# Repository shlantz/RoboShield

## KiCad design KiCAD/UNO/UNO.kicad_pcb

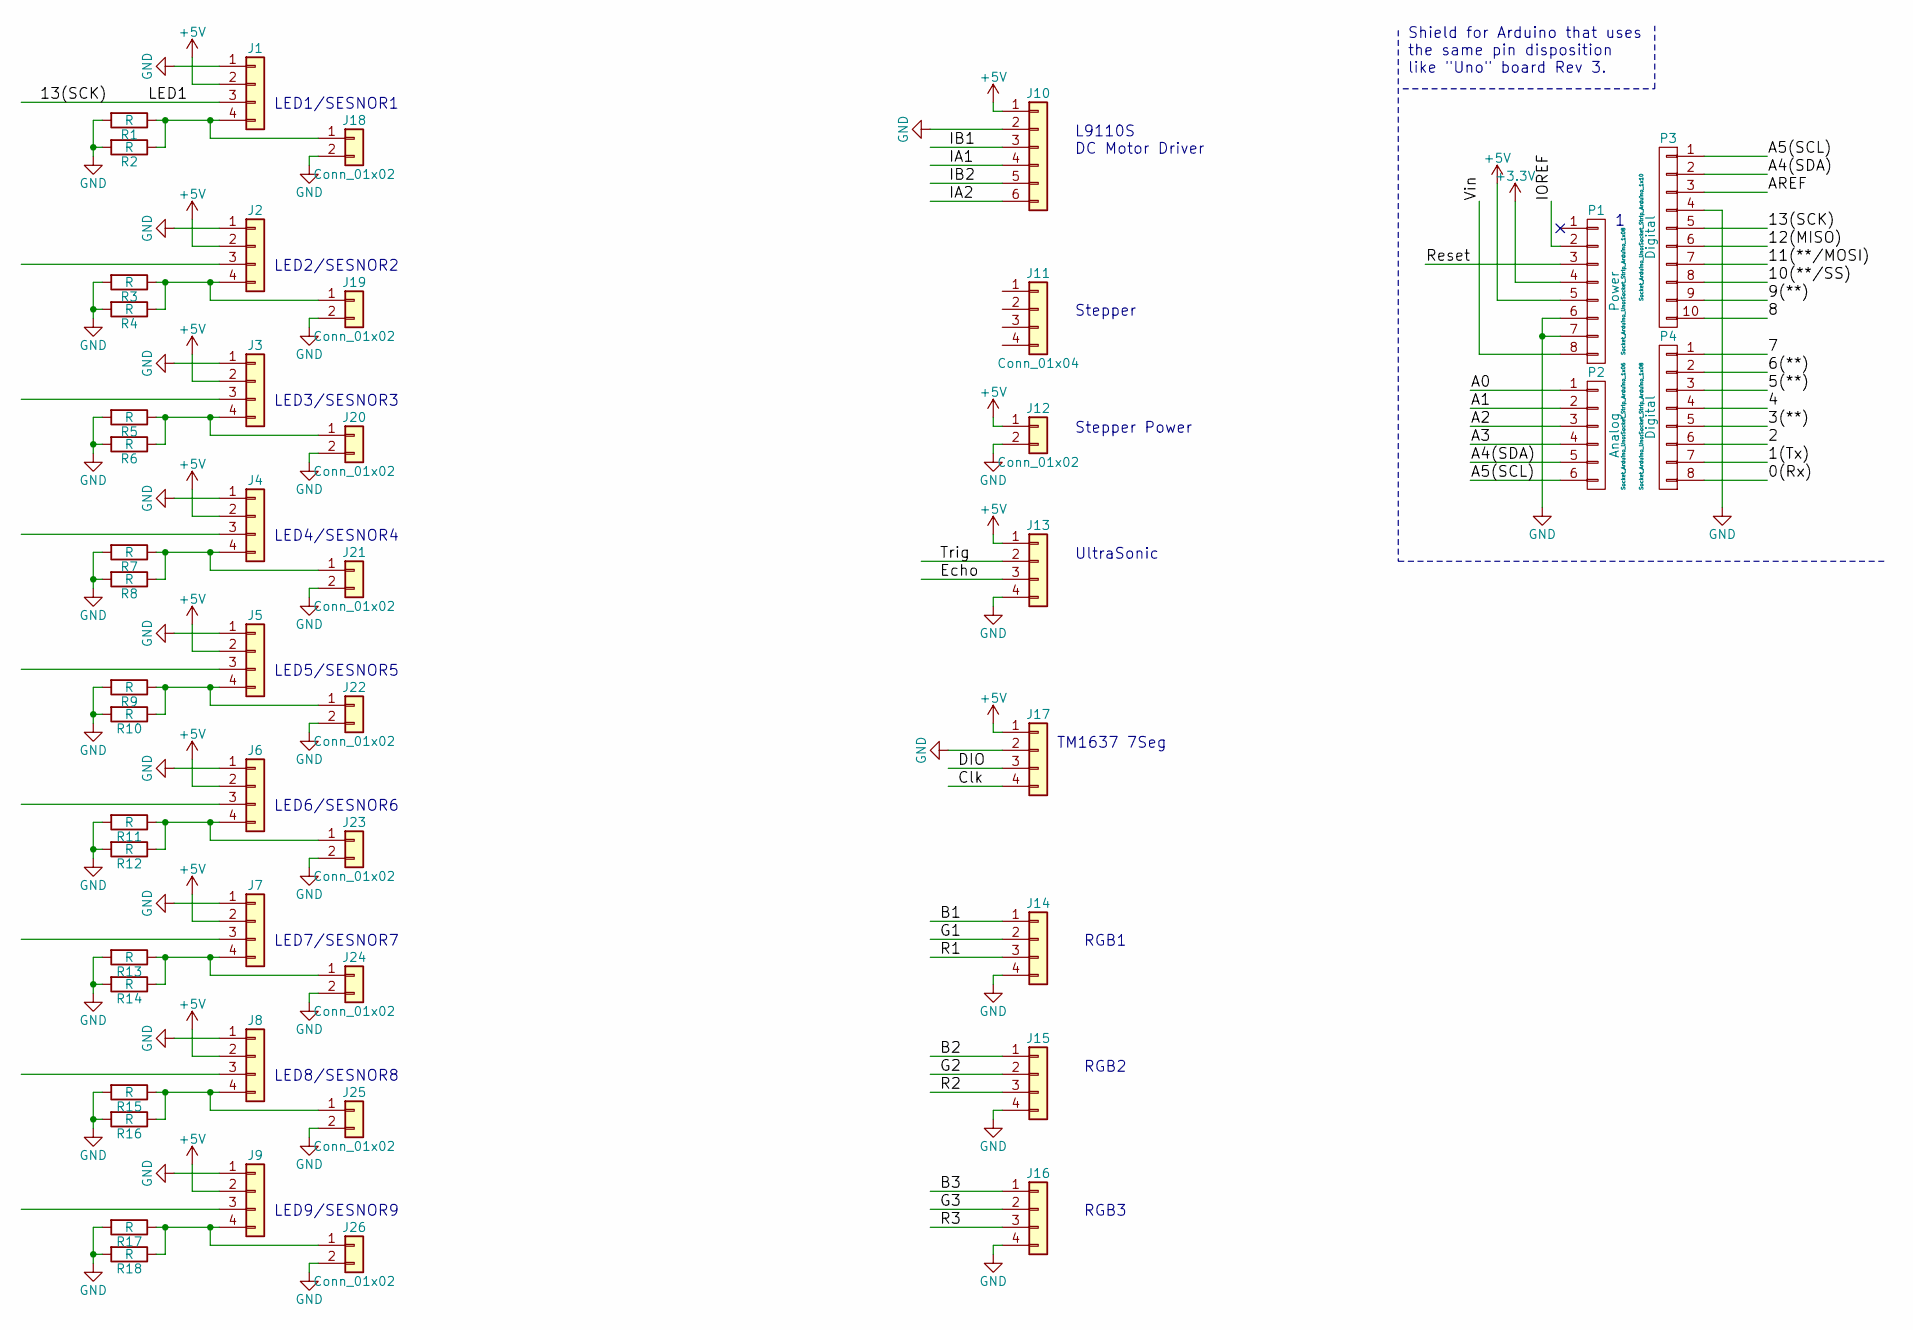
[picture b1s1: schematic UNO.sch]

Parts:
J1, J2, J3, J4, J5, J6, J7, J8, J9, J14, J15, J16, J17: Conn_01x04; Socket_Strip_Angled_1x04_Pitch2.54mm
J10: Conn_01x06; Socket_Strip_Straight_1x06_Pitch2.54mm
J11, J13: Conn_01x04; Socket_Strip_Straight_1x04_Pitch2.54mm
J12: Conn_01x02; Socket_Strip_Straight_1x02_Pitch2.54mm
J18, J19, J20, J21, J22, J23, J24, J25, J26: Conn_01x02; Pin_Header_Straight_1x02_Pitch2.54mm
P1: Power; Socket_Strip_Arduino_1x08
P2: Analog; Socket_Strip_Arduino_1x06
P3: Digital; Socket_Strip_Arduino_1x10
P4: Digital; Socket_Strip_Arduino_1x08
R1, R3, R5, R7, R9, R11, R13, R15, R17: R; R_0603_HandSoldering
R2, R4, R6, R8, R10, R12, R14, R16, R18: R; R_Axial_DIN0204_L3.6mm_D1.6mm_P5.08mm_Horizontal

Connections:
+3V3: P1.4
+5V: J1.2, J2.2, J3.2, J4.2, J5.2, J6.2, J7.2, J8.2, J9.2, J10.1, J12.1, J13.1, J17.1, P1.5
/0(Rx): P4.8
/1(Tx): P4.7
/2: P4.6
/3(**): P4.5
/4: P4.4
/5(**): P4.3
/6(**): P4.2
/7: P4.1
/8: P3.10
/9(**): P3.9
/10(**/SS): P3.8
/11(**/MOSI): P3.7
/12(MISO): P3.6
/13(SCK): J1.3, P3.5
/A0: P2.1
/A1: P2.2
/A2: P2.3
/A3: P2.4
/A4(SDA): P2.5, P3.2
/A5(SCL): P2.6, P3.1
/AREF: P3.3
/B1: J14.1
/B2: J15.1
/B3: J16.1
/Clk: J17.4
/DIO: J17.3
/Echo: J13.3
/G1: J14.2
/G2: J15.2
/G3: J16.2
/IA1: J10.4
/IA2: J10.6
/IB1: J10.3
/IB2: J10.5
/IOREF: P1.2
/R1: J14.3
/R2: J15.3
/R3: J16.3
/Reset: P1.3
/Trig: J13.2
/Vin: P1.8
GND: J1.1, J2.1, J3.1, J4.1, J5.1, J6.1, J7.1, J8.1, J9.1, J10.2, J12.2, J13.4, J14.4, J15.4, J16.4, J17.2, J18.2, J19.2, J20.2, J21.2, J22.2, J23.2, J24.2, J25.2, J26.2, P1.6, P1.7, P3.4, R1.2, R2.2, R3.2, R4.2, R5.2, R6.2, R7.2, R8.2, R9.2, R10.2, R11.2, R12.2, R13.2, R14.2, R15.2, R16.2, R17.2, R18.2
unnamed: J1.4, J18.1, R1.1, R2.1
unnamed: J2.4, J19.1, R3.1, R4.1
unnamed: J3.4, J20.1, R5.1, R6.1
unnamed: J4.4, J21.1, R7.1, R8.1
unnamed: J5.4, J22.1, R9.1, R10.1
unnamed: J6.4, J23.1, R11.1, R12.1
unnamed: J7.4, J24.1, R13.1, R14.1
unnamed: J8.4, J25.1, R15.1, R16.1
unnamed: J9.4, J26.1, R17.1, R18.1

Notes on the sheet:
Shield for Arduino that uses the same pin disposition like "Uno" board Rev 3.
LED1/SESNOR1
LED2/SESNOR2
LED3/SESNOR3
LED4/SESNOR4
LED5/SESNOR5
LED6/SESNOR6
LED7/SESNOR7
LED8/SESNOR8
LED9/SESNOR9
L9110S DC Motor Driver
Stepper
Stepper Power
UltraSonic
RGB2
RGB3
RGB1
TM1637 7Seg

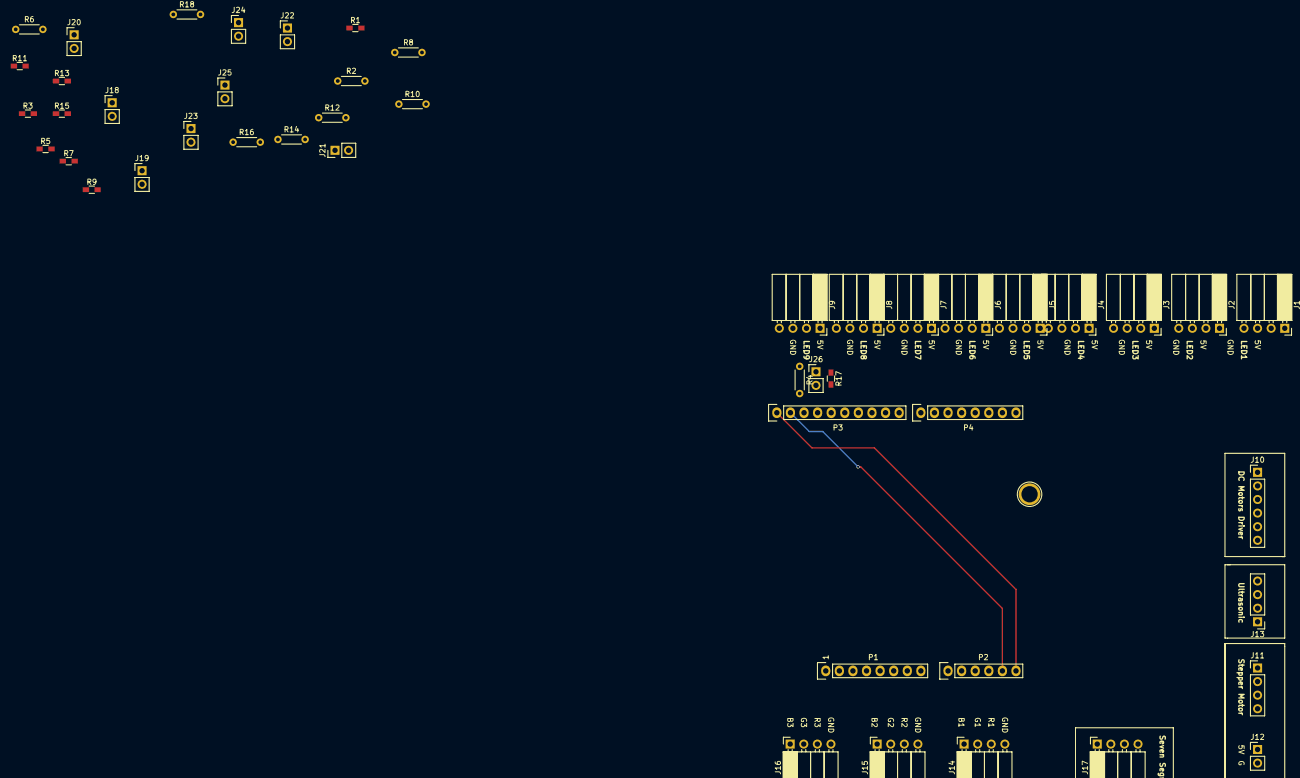
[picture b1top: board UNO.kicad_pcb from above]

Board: 2 copper layers, 49 parts (0 on the bottom side), 14 nets.

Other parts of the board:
P8: CONN_01X01; Arduino_1pin

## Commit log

2018-02-15 First Revision
2018-02-15 Adding LED Connectors
2018-02-15 9 LEDs Added and Motor Connector
2018-02-16 More connctors added
2018-02-18 Sensor/LED connctor changed to 4 pin to support more options
2018-02-25 no message
